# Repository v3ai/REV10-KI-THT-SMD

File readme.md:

These are the Kicad files for the REV-10 NSE Geiger Counter

if you wanna manufacture with jlcpcb make sure you use this (or just the included zip file)

https://jlcpcb.com/help/article/362-how-to-generate-gerber-and-drill-files-in-kicad-7

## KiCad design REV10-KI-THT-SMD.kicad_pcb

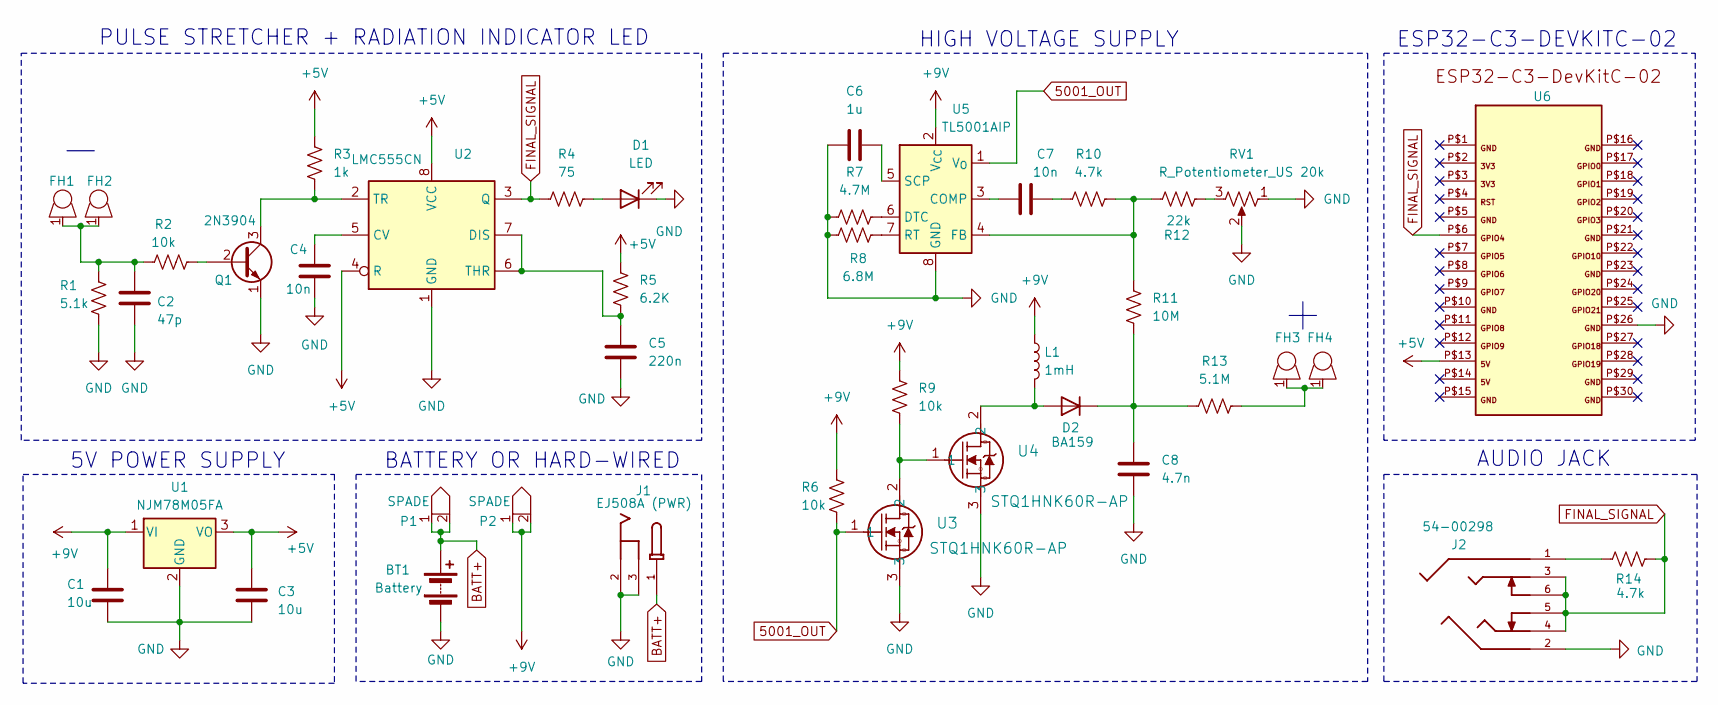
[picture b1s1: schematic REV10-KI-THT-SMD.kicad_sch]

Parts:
BT1: Battery; BatteryHolder_MPD_BA9VPC_1xPP3
C1, C3: 10u; C_THT_SMD
C2: 47p; C_THT_SMD
C4, C7: 10n; C_THT_SMD
C5: 220n; C_THT_SMD
C6: 1u; C_THT_SMD
C8: 4.7n; CHV
D1: LED; LED_D3.0mm
D2: BA159; D_DO-41_SOD81_P7.62mm_Horizontal
FH1, FH2, FH3, FH4: 36-3530-ND
J1: EJ508A (PWR); MPD_EJ508A; PARTREV J
J2: 54-00298; PARTREV A
L1: 1mH; L_Radial_D8.7mm_P5.00mm_Fastron_07HCP
P1, P2: SPADE; 0197084013
Q1: 2N3904; TO-92_Inline_Wide
R1: 5.1k; R_BIG
R2, R6, R9: 10k; R_SMALL
R3: 1k; R_SMALL
R4: 75; R_SMALL
R5: 6.2K; R_SMALL
R7: 4.7M; R_SMALL
R8: 6.8M; R_SMALL
R10, R14: 4.7k; R_SMALL
R11: 10M; R_SMALL
R12: 22k; R_SMALL
R13: 5.1M; R_SMALL
RV1: R_Potentiometer_US 20k; POT_3362P
U1: NJM78M05FA; TO-220-3_Vertical
U2: LMC555CN; DIP-8_W7.62mm
U3, U4: STQ1HNK60R-AP; TO-92_Inline_Wide
U5: TL5001AIP; DIP-8_W7.62mm
U6: ESP32-C3-DEVKITC-02HOLES; ESP32-C3-DevKitC-02

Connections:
5001_OUT: R6.2, U3.1, U5.1 (V_{O})
+5V: C3.1, R3.1, R5.1, U1.3 (VO), U2.4 (R), U2.8 (VCC), U6.P$13
+9V: C1.1, L1.1, P2.1, P2.2, R6.1, R9.1, U1.1 (VI), U5.2 (V_{CC})
BATT+: BT1.1 (+), J1.1, P1.1, P1.2
FINAL_SIGNAL: J2.3, J2.4, J2.5, J2.6, R4.1, R14.2, U2.3 (Q), U6.P$6
GND: BT1.2 (-), C1.2, C2.2, C3.2, C4.1, C5.2, C6.1, C8.2, D1.1 (K), J1.2, J1.3, J2.2, Q1.1 (E), R1.2, R7.1, R8.1, RV1.1, RV1.2, U1.2 (GND), U2.1 (GND), U3.3, U4.3, U5.8 (GND), U6.P$26
unnamed: C2.1, FH1.1, FH2.1, R1.1, R2.1
unnamed: C7.2, R10.1
unnamed: D1.2 (A), R4.2
unnamed: D2.2 (A), L1.2, U4.2
unnamed: C8.1, D2.1 (K), R11.2, R13.1
unnamed: FH3.1, FH4.1, R13.2
unnamed: J2.1, R14.1
unnamed: Q1.2 (B), R2.2
unnamed: Q1.3 (C), R3.2, U2.2 (TR)
unnamed: R9.2, U3.2, U4.1
unnamed: R12.2, RV1.3
unnamed: C4.2, U2.5 (CV)
unnamed: C5.1, R5.2, U2.6 (THR), U2.7 (DIS)
unnamed: C7.1, U5.3 (COMP)
unnamed: R7.2, U5.6 (DTC)
unnamed: R10.2, R11.1, R12.1, U5.4 (FB)
unnamed: R8.2, U5.7 (RT)
unnamed: C6.2, U5.5 (SCP)

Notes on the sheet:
HIGH VOLTAGE SUPPLY
AUDIO JACK
BATTERY OR HARD-WIRED
ESP32-C3-DEVKITC-02
PULSE STRETCHER + RADIATION INDICATOR LED
5V POWER SUPPLY

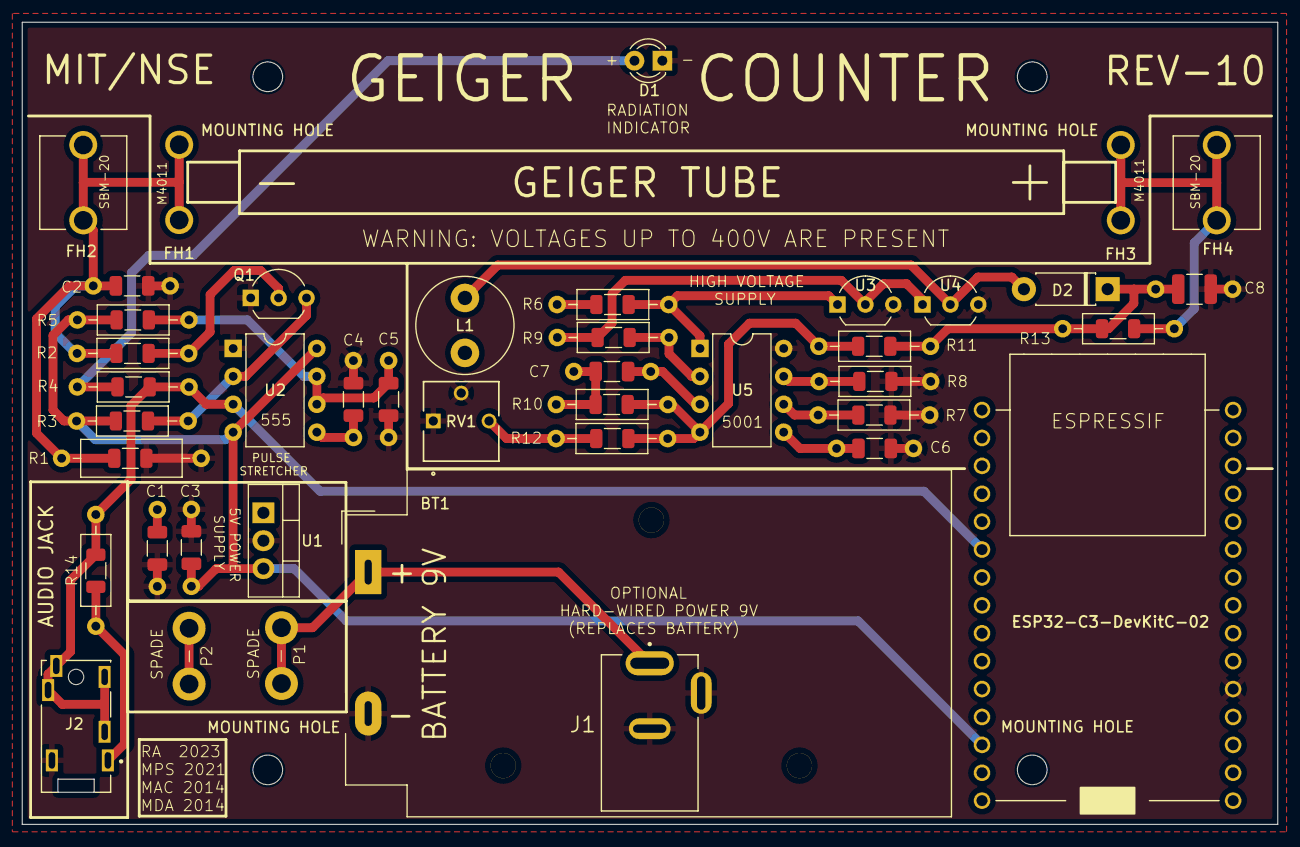
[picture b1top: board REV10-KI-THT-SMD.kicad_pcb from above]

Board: 2 copper layers, 114.3 x 73.0 mm, 46 parts (0 on the bottom side), 24 nets.

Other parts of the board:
MOUNTING HOLE: MountingHole_2.7mm
MOUNTING HOLE#2, MOUNTING HOLE#3, MOUNTING HOLE#4: MountingHole_2.7mm

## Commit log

2024-07-09 already some changes june 9 first comm
2024-07-12 first dual
2024-07-20 added holes for m4011, removed rev 9 backups
2024-07-20 added readme
2024-07-20 small updates, name, moving j1 a small bit
2024-07-24 changed 10nf to 15nf, realized the old design had that cap as 15, trying to stay true
2024-07-31 july 31st
